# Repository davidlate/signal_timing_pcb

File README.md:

# Signal Timing PCB
This is a project to produce repeated audio pulses which are precisely timed with the outputs of two
current regulated, square wave AC outputs

This repo is divided into header files and functions for the various parts of the project to allow for testing each component individually

-sdcard operations
-I2S op
-DAC ops
-RMT ops
-GPTimer ops

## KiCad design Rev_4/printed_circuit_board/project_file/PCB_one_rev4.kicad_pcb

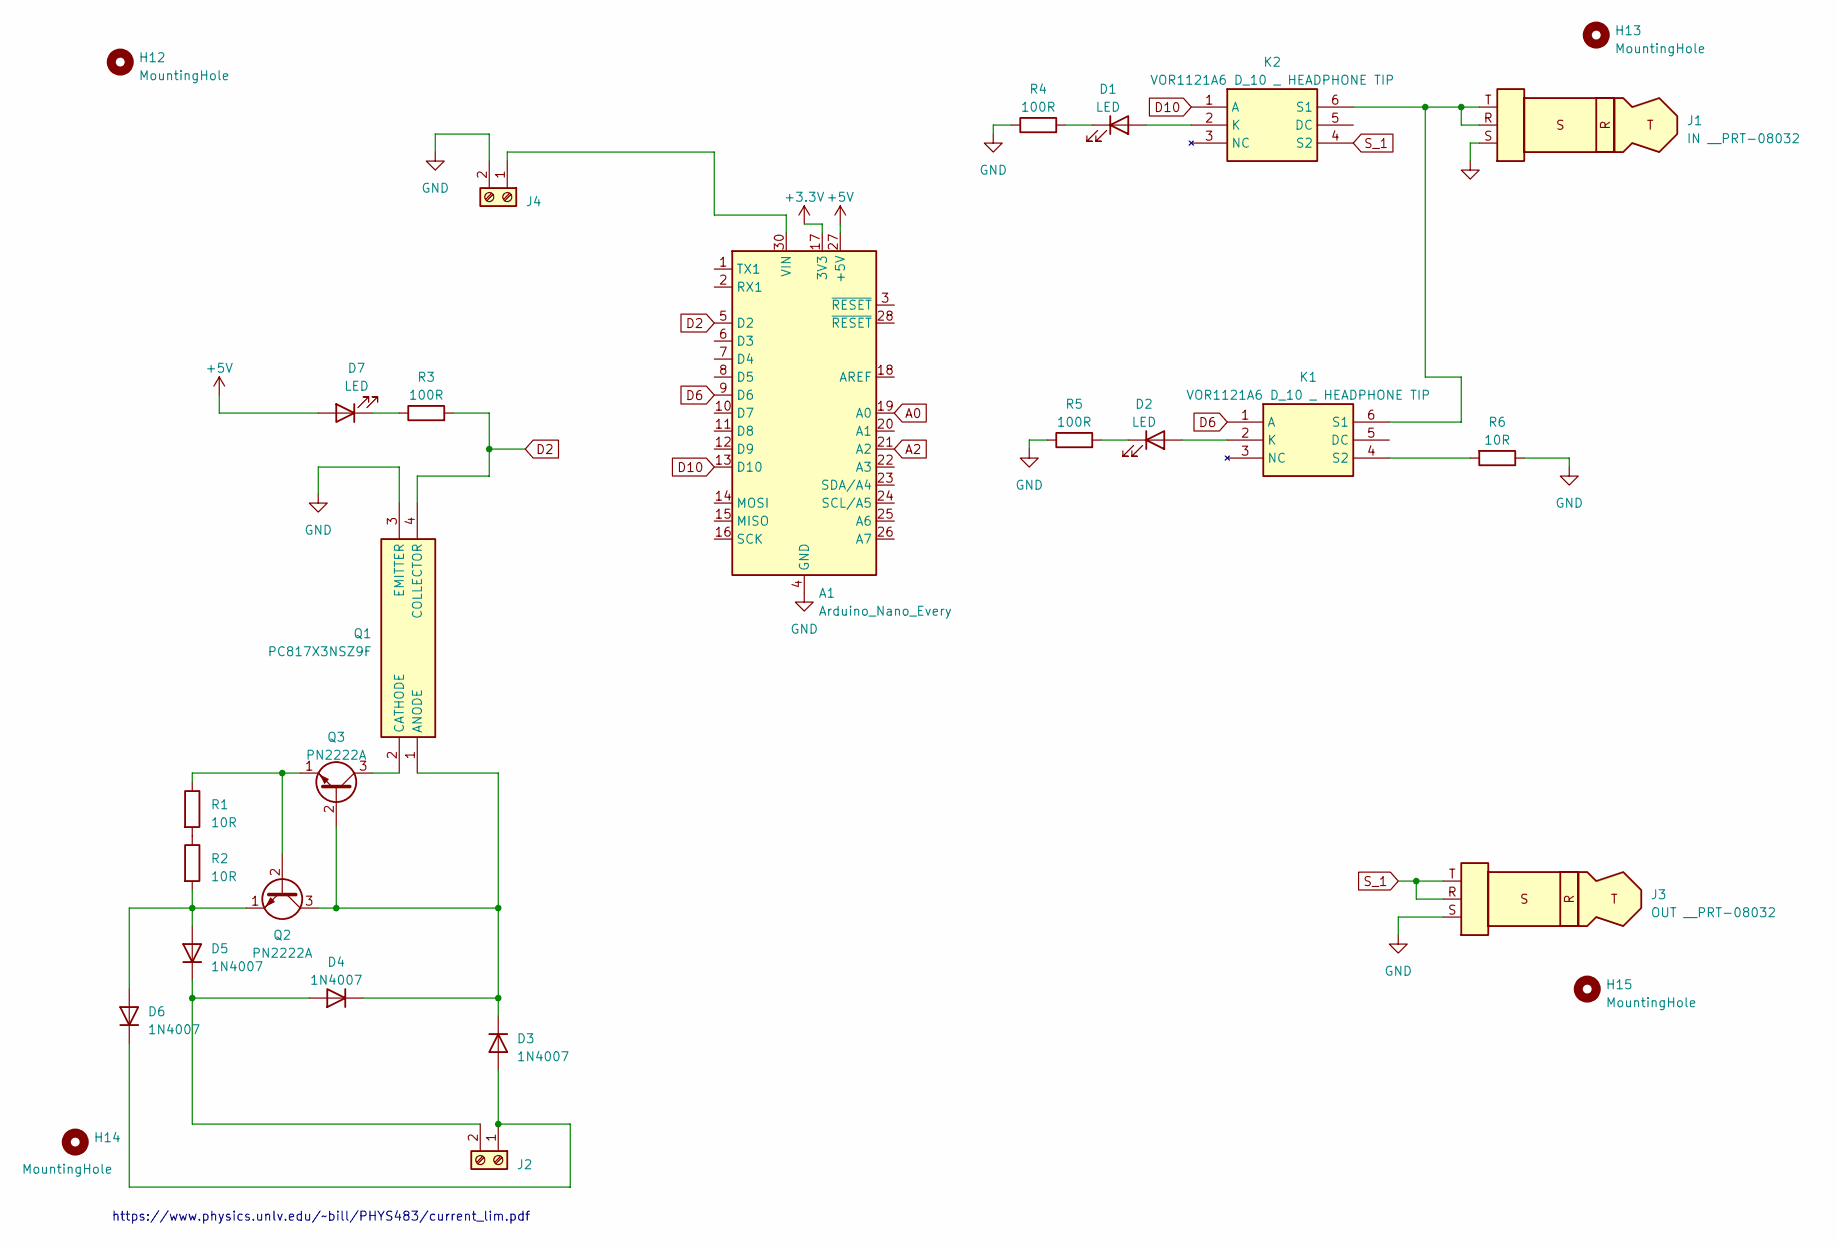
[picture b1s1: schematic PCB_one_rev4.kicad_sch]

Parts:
A1: Arduino_Nano_Every; Arduino_Nano
D1, D2, D7: LED; D_A-405_P7.62mm_Horizontal
D3, D4, D5, D6: 1N4007; D_A-405_P7.62mm_Horizontal
H12, H13, H14, H15: MountingHole; MountingHole_3.2mm_M3
J1: IN __PRT-08032; PRT-08032
J2, J4: R_Axial_DIN0204_L3.6mm_D1.6mm_P5.08mm_Horizontal
J3: OUT __PRT-08032; PRT-08032
K1, K2: VOR1121A6 D_10 _ HEADPHONE TIP; DIP-6_W7.62mm; Mouser Part Number 78-VOR1121A6
Q1: PC817X3NSZ9F; DIP-4_W7.62mm; Manufacturer_Part_Number PC817X3NSZ9F; Mouser Part Number 852-PC817X3NSZ9F
Q2, Q3: PN2222A; TO-92_Inline
R1, R2, R6: 10R; R_Axial_DIN0204_L3.6mm_D1.6mm_P7.62mm_Horizontal
R3, R4, R5: 100R; R_Axial_DIN0204_L3.6mm_D1.6mm_P7.62mm_Horizontal

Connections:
+3.3V: A1.17 (3V3)
+5V: A1.27 (+5V), D7.2 (A)
A0: A1.19 (A0)
A2: A1.21 (A2)
D2: A1.5 (D2), Q1.4 (COLLECTOR), R3.2
D6: A1.9 (D6), K1.1 (A)
D10: A1.13 (D10), K2.1 (A)
GND: A1.4 (GND), A1.29 (GND), J1.S, J3.S, J4.2, Q1.3 (EMITTER), R4.1, R5.1, R6.1
unnamed: A1.30 (VIN), J4.1
unnamed: D1.2 (A), K2.2 (K)
unnamed: D1.1 (K), R4.2
unnamed: D2.2 (A), K1.2 (K)
unnamed: D2.1 (K), R5.2
unnamed: D3.2 (A), D6.1 (K), J2.1
unnamed: D3.1 (K), D4.1 (K), Q1.1 (ANODE), Q2.3 (C), Q3.2 (B)
unnamed: D4.2 (A), D5.1 (K), J2.2
unnamed: D5.2 (A), D6.2 (A), Q2.1 (E), R2.2
unnamed: D7.1 (K), R3.1
unnamed: J1.R, J1.T, K1.6 (S1), K2.6 (S1)
unnamed: K1.4 (S2), R6.2
unnamed: Q1.2 (CATHODE), Q3.3 (C)
unnamed: Q2.2 (B), Q3.1 (E), R1.1
unnamed: R1.2, R2.1
S_1: J3.R, J3.T, K2.4 (S2)

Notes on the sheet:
https://www.physics.unlv.edu/~bill/PHYS483/current_lim.pdf

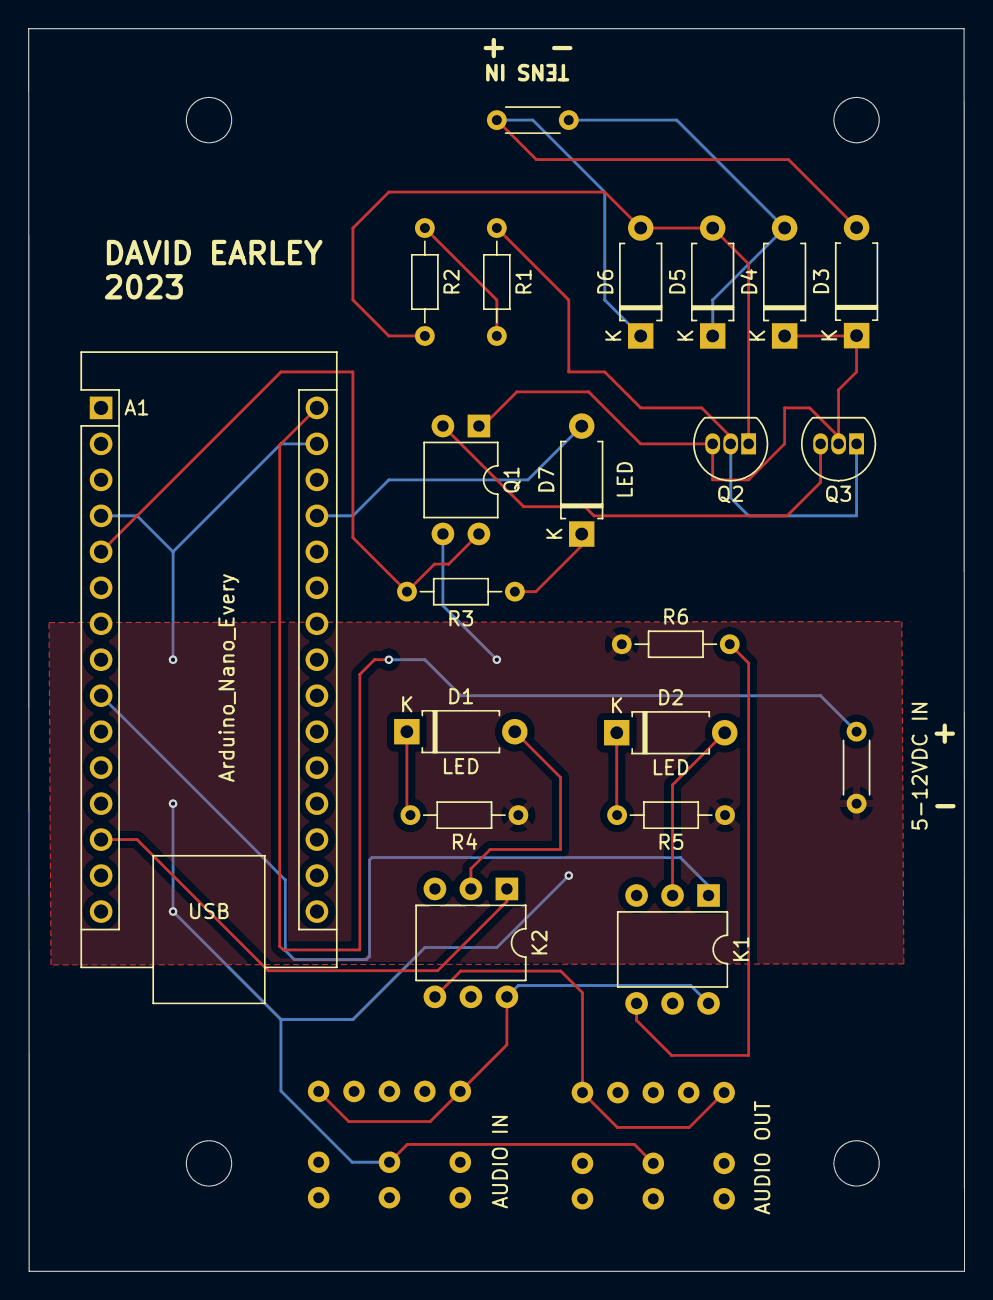
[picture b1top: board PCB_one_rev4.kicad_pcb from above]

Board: 2 copper layers, 66.1 x 87.7 mm, 27 parts (0 on the bottom side), 21 nets.

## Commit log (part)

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2023-11-05 Initial release
2024-03-29 Re-organized folder
2024-03-29 Added software
2024-03-29 Added fixture CAD model
2024-10-22 Intial move of project to github
2024-10-22 Added all files to repo as part of initialization
2024-10-22 One more push
2024-10-22 One more try
2024-10-22 renamed rmt peripheral test
2024-10-27 Adding all files
2024-10-27 Testing Git Branching with comment
2024-10-27 Comfirmed that auto_clear_after_cb works to clear buffer. Still some delay in writing
2024-10-27 auto_clear_before_cb seems to work the same way, with the same delay
2024-10-27 Moved i2s write from task into main
2024-10-27 Cleaned up code, added comments, improved timekeeping. This one works
2024-10-27 Fixed callocs and otehr housekeeping. Tested increasing waveform duration but stack size isn't big enough. This one works
2024-10-27 Updated delay
2024-10-27 Got I2S working on ESP32 - S3
2024-11-02 Updated RMT Test with trimming to improve suynchronization of channels. Confirmed that synchronization works with the ESP32-S3
2024-11-02 Confirmed Effectiveness of using I2S with RMT. Currently, closest delay is 12.5ms
2024-11-02 Increased sample rate to 44100. Delay between sound and pulse increased to 20ms. Seems to be issue with i2s
2024-11-02 Updated, code is working except for the delay timing. Connection issues cause false alarms w.r.t. i2s working
2024-11-08 Updating
2024-11-09 Corrected 20 ms delay after I2S write. Sum of I2S buffer must be equal to the length of the payload. auto-clear true. don't enable/disable with every write
2024-11-15 Got GPTimer working to toggle GPIO 17. Neither RMT nor I2S work in GPTimer ISR. Will need to manipulate registers manually.
2024-11-15 Disabled watchdog timer
2024-11-15 Removed sound_struct
2024-11-15 Put sound_struct back in
2024-11-15 Updated I2S function to include more precise time tracking. Added busy waits to main function. Needs to be refactored
2024-11-15 Functionally, the timing has been resolved here
2024-12-01 Got audio playing again
2024-12-01 Audio working on ESP23-S3 Seeeduino
2024-12-01 Began attempting to write to i2s using stereo. Still having issues with both frequencies playing on each channel
2024-12-01 Got audio transmitting in stereo. The issue lay in teh quality of the headphone jack. The jack terminals were picking up both signals, even though the software was correct
2024-12-04 Added volume control with potentiometer
2024-12-06 Updated i2s_common.c and .h to create ISR-safe version of I2s write. Proved functionality. Began writing RTOS queue handling to use it with GPTimer more robustly
2024-12-06 Got i2s queue send/receive into a buildable state
2024-12-06 Commented code and simplified variable names in I2s play task and GPtimer callback
2024-12-06 Added comments and updated variable names to i2s_p lay task to be more clear.
2024-12-06 Added comments on buff_pos
2024-12-06 Corrected calculation of sine wave to add cos^2 multiplier
2024-12-06 Renamed the amplitude var to be more descriptive.
2024-12-06 Commented out main for loop
2024-12-06 Added volume control
2024-12-08 THIS IS A GOOD AUDIO CONFIGURATION. AUDIO SOUNDS GOOD IN THIS COMMIT
2024-12-08 Added cos^2 ramp. No apparent effect, but audio still sounds good. Some minor popping still but nothing crazy
2024-12-08 Tried moving gp timer enable into i2s_play task, but not convinced it will work well. The audio plays at regular intervals, however more attention will be needed to how the i2s write is set up. The r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
2024-12-08 Still having issues ironing out the i2s_write. In this version, the audio sounds good althgouh the ESP complains about the DMA buff size
2024-12-08 This plays audio acceptably
2024-12-09 Got I2S working with the GPTimer interrupts. Figured out weird behavior with the preload - it had to do with mixing "words" and bytes. Fixed now. Need to work on audio fade
2024-12-10 Fixed issue with audio distorting when volume change - was an implicit type conversion error. Still working on adding multiple frequencies; amplitudes seem to sum instead of averaging
2025-01-12 SOLVED! The audio popping issue. This works with the PCM5102A. There is a need for an output amp to buffer the signal, and I used Shure in ear monitors. The cos^2 ramp is also correct now. Still work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
2025-02-28 bringing repo up to current rev
2025-07-06 Reorganized folder structure and added folder for SD card operations
2025-07-07 Implemented a rough wave file parser and confirmed its functionality on the device. Started on the rng implementation of selecting chunks of the audio file.
2025-07-08 Added function to grab and return randomly selected chunk of audio file
2025-07-11 Finished audio chunk functionality
2025-07-11 Debugged and fixed audio chunk getter function
2025-07-15 Completed first pass of i2s write and preload functions
2025-07-19 I2S writing with preload is mostly working. More work is needed to overcome issues with soft mute of PCM5102a chip.
    Former-commit-id: 3380aa73cd6dc00d4ae94a5da3eee82436e23942
2025-07-19 Got most of i2s operations working - need to do some more work to overcome issues with the PCM5102a's soft mute.
    Former-commit-id: 5eb8c539820400e6e8f0e4b53885ee9a46c9e219
2025-07-19 Got most of i2s operations working - need to do some more work to overcome issues with the PCM5102a's soft mute.
    Former-commit-id: decff694581d2191cfd28964b4b6ac9335b6b3f9
2025-07-19 Got most of i2s operations working - need to do some more work to overcome issues with the PCM5102a's soft mute.
    Former-commit-id: 773c6e1246937249065e0b8cf525007fdf8654cd
2025-07-31 Got I2S output working, using 30ms of dither to overcome power-up artefacts
    Former-commit-id: 7cbd1f22fb0ea0932767ffc88d02489cd193fc80
2025-07-31 Reset project - poor behavior with audio turn-on has returned. Unclear what the cause is
2025-08-01 Changed preload function, and messed with dither function. Increasing dither_num_samples /decreases/ the actual amount of dither, bizarrely
2025-08-01 Added line on write functions to compensate for chunk pos if buffer is not completely written to i2s bus
2025-08-01 Dither solution is on the way. The dither const of 1 was being multiplied by the vol scale factor of .1, then rounded down due to implicit type conversion
2025-08-06 Implemented a separate file to handle adc operations - got the adc for the volume control and ch1 knob working.
2025-08-09 Began implementing queue-based volume output with terminal display. Hid terminal cursor
2025-08-19 Updated code with outline of how memory management will be implemented for longer audio files Not finished - need to update "play_audio_chunk" function
2025-10-05 Changed adc read sync from queue to mutex. Fixed alignment of fread buffer updates. Still having issues getting full audio to play
2025-10-09 Added function to reload memory buffer in parallel with playing from I2s bus. Haven't implemented it yet
2025-10-11 Multi-threaded loading of audio files confirmed to be working. Playing audio chunk of 1 second in length successfully. Confirmed that data being sent is correct
2025-10-11 Got the cos^2 rise fall funcationality working
2025-10-16 Added some of the bones for the recurring audio GPTImer alarm
2025-10-19 Got audio playing with GPTimer
2025-11-14 Added PWM and started to get it working. Revert to here if needed.
2026-02-20 Changed CMake file to add more gcc error checking flags
2026-02-22 Converted main to c++, sorted out a number of new compiler errors. Encountered lingering issue with .rise_fall_num_samples causing a gap in the audio playback. But the RMT and audio are timed precise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
